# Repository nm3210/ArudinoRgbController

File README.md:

# Arudino Rgb(w) Project Collection
This repository contains a bunch of projects that I've created over the years for controlling various RGB (and sometimes RGBW) LED projects using arduinos uno's/teensy's. I have primarily been using the Eclipse-based [Sloeber](http://eclipse.baeyens.it/stable.php?OS=Windows) Arduino IDE which makes programming in C++ for the arduino platform much eaiser (especially if you're used to Eclipse).

## Main Projects:
* [ArudinoRgbController](ArudinoRgbController): This contains the original Atmega328 arduino (duo/uno) code that was used on a project to control some RGB LEDs (the simple four-lead ones) based on the time from a real-time clock (RTC) input. 

    The idea was to be a 'Visual Alarm', inasmuch that the LEDs would change color based on the time during the day. For this project, I also designed a circuit board with all the necessary RTC inputs and power for the LEDs which can be found on OSH Park [here](https://oshpark.com/shared_projects/ZrMcpgAp) (images of the circuit board below). 

* [RgbControllerWithIR](RgbControllerWithIR): This is an extension of the above ArudinoRgbController project that adds in the [IRremote library](https://github.com/z3t0/Arduino-IRremote) in order to control the colors a little easier.

    A *big* note: it was necessary to move the output pin for the blue RGB from pin 11 to pin 5 because of a conflict with the internal timer libraries and the IRremote ([see issue here](https://github.com/z3t0/Arduino-IRremote/issues/251)). This change required me to physically ripup the connection between pin 11 and the blue led transistor and then white wire a new connection to pin 5. Then the IR receiver was added to pin 2.

## Testing & Prototyping Projects:
### NeoPixel (WS2812B/SK6812, specifically RGBW strips)
* [NeoPixelTesting](NeoPixelTesting): This project plays around with the NeoPixel RGBW LED strips. I initially bought the [AdaFruit](https://www.adafruit.com/products/2868) stick of eight but eventually bought a roll of them off ebay (5m of 30LEDs/m).
* [MultiSegmentTesting](MultiSegmentTesting): This is an extension of the NeoPixelTesting project that adds in the ability to split up the strip into differnt arbitrary-length segments.

### RTC (DS1307)
* [RTC_SetTime](RTC_SetTime): Set/initialize the time of the DS1307 to the time at compile.
* [RTC_ReadTime](RTC_ReadTime): Read back the time on the DS1307 with the ability to add in extra seconds with a button press.
* [RTC_AlarmTesting](RTC_AlarmTesting): Test the [TimeAlarm](https://github.com/PaulStoffregen/TimeAlarms) library with the DS1307.

### Other/Misc
* [IrRemoteTesting](IrRemoteTesting): Test the incorporation of an IR receiver on an arduino.
* [ButtonTesting](ButtonTesting): Test the use of the AIN0 comparator on the atmega328 for use as a button.
* [HsiColor](HsiColor): Establishes the 'HSI' colorspace (from [here](http://blog.saikoled.com/post/43693602826/why-every-led-light-should-be-using-hsi)) instead of direct RGB, making it easier to do crossfading (used in the ArduinoRgbController project).

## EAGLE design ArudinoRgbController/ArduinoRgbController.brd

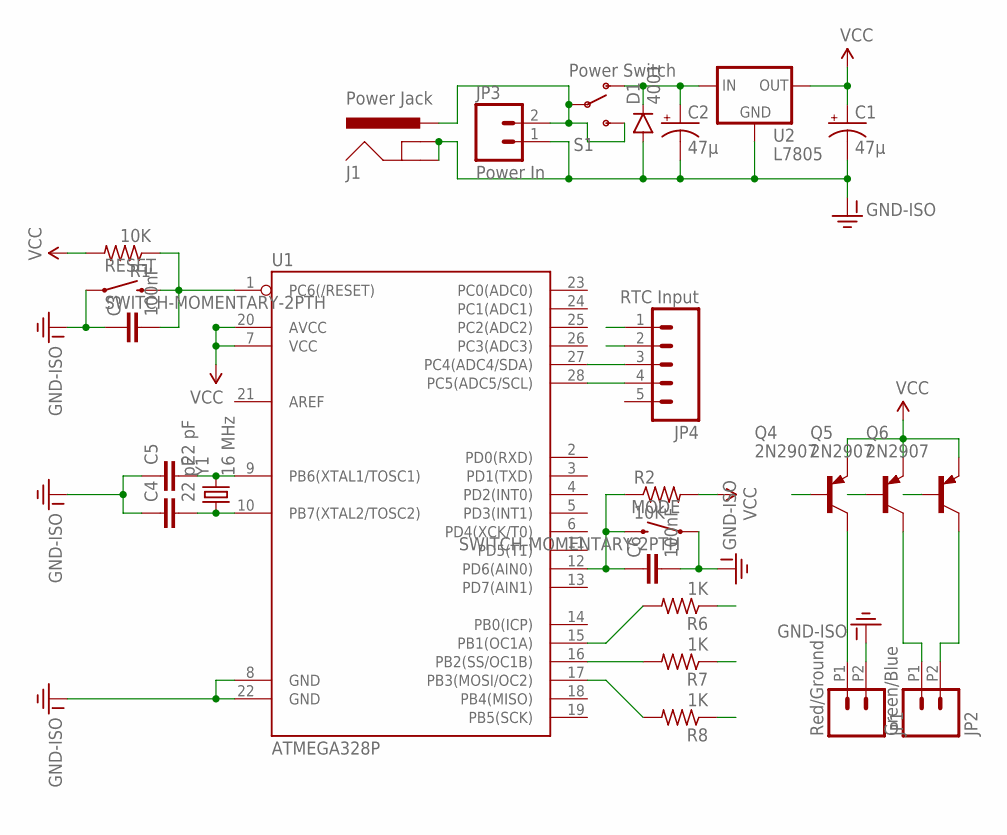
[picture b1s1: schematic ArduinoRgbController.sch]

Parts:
C1, C2: 47μ; ELECTROLYTIC_CAP
C3, C6: 100nF; CAP-PTH-SMALL
C4, C5: 22 pF; CAP-PTH-SMALL
D1: 4001; DIODE-1N4001
J1: Power Jack; POWER_JACK
JP1: Red/Ground; 1X02_2.54_SCREWTERM
JP2: Green/Blue; 1X02_2.54_SCREWTERM
JP3: Power In; SCREWTERMINAL-5MM-2
JP4: RTC Input; 1X05_LONGPADS
MODE: SWITCH-MOMENTARY-2PTH; TACTILE-PTH
Q4, Q5, Q6: 2N2907; TO92-EBC-OVAL
R1, R2: 10K; 0207/9
R6, R7, R8: 1K; 0207/9
RESET: SWITCH-MOMENTARY-2PTH; TACTILE-PTH
S1: Power Switch; SWITCH-SPDT
U1: ATMEGA328P; DIL28-3
U2: L7805; 78XXL
Y1: 16 MHz; HC49US

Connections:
BLUE: Q6.B, R8.1
BLUE_LINE: R8.2, U1.17 (PB3(MOSI/OC2))
BLUE_OUT: JP2.P2 (2), Q6.C
GND-ISO: C1.-, C2.-, C3.1, C4.1, C5.1, C6.2, D1.A, J1.GND, J1.GNDBREAK, JP1.P2 (2), JP3.1, JP4.1, MODE.1, RESET.1, U1.8 (GND), U1.22 (GND), U2.GND
GREEN: Q5.B, R7.1
GREEN_LINE: R7.2, U1.16 (PB2(SS/OC1B))
GREEN_OUT: JP2.P1 (1), Q5.C
unnamed: C5.2, U1.9 (PB6(XTAL1/TOSC1)), Y1.2
unnamed: C4.2, U1.10 (PB7(XTAL2/TOSC2)), Y1.1
PC4: JP4.3, U1.27 (PC4(ADC4/SDA))
PC5: JP4.4, U1.28 (PC5(ADC5/SCL))
RED: Q4.B, R6.1
RED_LINE: R6.2, U1.15 (PB1(OC1A))
RED_OUT: JP1.P1 (1), Q4.C
RESET_LINE: C3.2, R1.1, RESET.3 (2), U1.1 (PC6(/RESET))
SWITCH_LINE: C6.1, MODE.3 (2), R2.1, U1.12 (PD6(AIN0))
VCC: C1.+, JP4.2, Q4.E, Q5.E, Q6.E, R1.2, R2.2, U1.7 (VCC), U1.20 (AVCC), U2.OUT
VIN_POSTSWITCH: C2.+, D1.C, S1.1 (O), U2.IN
VIN_PRESWITCH: J1.PWR, JP3.2, S1.2, S1.3 (S)

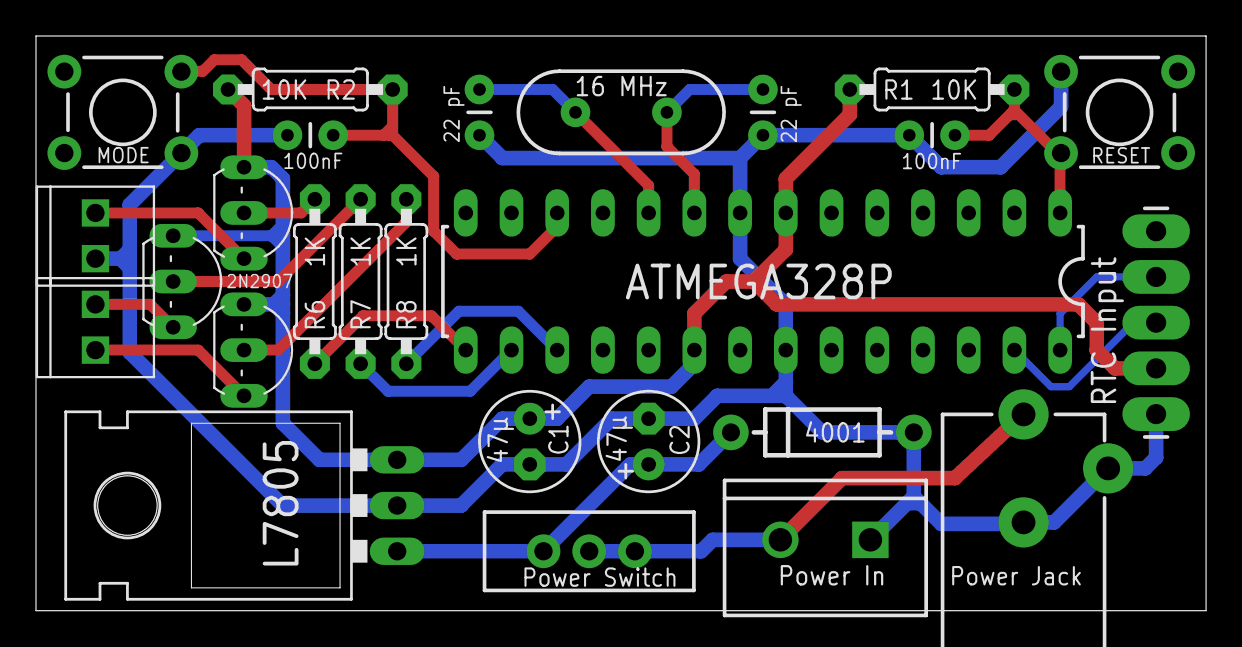
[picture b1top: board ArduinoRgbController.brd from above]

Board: 2 copper layers, 65.0 x 31.9 mm, 26 parts (0 on the bottom side), 19 nets.

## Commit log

2016-08-06 Initial (clean) project
    Base barebones arduino c++ project.
2016-08-06 Update to 'Revision1'
    This revision incorporates some simple RGB fading based on some code I
    found on stack echange.
2016-08-06 Adding RTC functions
    This commit adds the 'ReadTime' and 'SetTime' arguino sketches to
    control the time of the DS1307 RTC.
2016-08-07 Update to 'Revision 2' - HSI mode
    This update changed a LOT of the underlying color logic. Instead of
    trying to work things out in RGB space, it converts things to HSI which
    allows some really easy looping of colors. A left a lot of commented out
    code in this commit (for various trail/errors) that will get cleaned up
    later.
2016-08-07 Adding other testing sketches
    Adding the 'ButtonTesting' sketch which was an attempt at trying to
    figure out how to do a long-press; it seems to work fine on my proto
    board, but not at all on the final PCB/wired one. This also adds the
    'HsiColor' sketch which is where I ironed out all the bugs to HSI before
    adding it to the main ArduinoRgbController.
2016-08-12 Disable 'dynamic mode'
    The dynamic mode will be a bit trickier to figure out, this commit
    disables the alarms, switch statement, and related functions.
2016-08-12 Fix to alarms not working; added functions
    This commit adds the 'Alarm.delay(0)' which was needed to make all the
    alarms work. I also updated the alarm times to be more practical and
    added a couple 'adjustInt' and 'adjustSat' functions to make it easier
    to change the properties of a color.
2016-08-13 Adding 'AlarmTesting' sketch
    This sketch (not currently working) will check for alarm flags during
    the loop. The purpose will be to not rely on the Alarm.alarmRepeat(..)
    that isn't quite as flexible as I woud like. Hopefully this implemention
    will make the 'dynamic mode' work able.
2016-08-13 Update to get the alarm checking working
    This updates the 'AlarmTesting' sketch to actually work! It's just a
    simple check for time-of-day now.
2016-08-14 Change to the new alarm handler
    This commit uses the new alarm handler that was established within the
    'RTC_AlarmTesting' sketch. It also reintroduces the 'dynamic mode' (for
    testing). I also cleaned up a lot of the old function/variables.
2016-08-14 Minor color changes and code cleanup.
    This changes the 'orange' and 'violet'/'purple' colors to be a bit
    brighter. Also cleaned up some comments here and there.
2016-08-14 Fix for the count variable looping around
    This issue caused the colors to jump to green to red abruptly when
    things wrapped around. The fix keeps the count variable contained with a
    modulo.
2017-01-30 Moved all functions in the h file to the cpp file
    Not sure why I felt the need to put functions in the header file, but
    this commit moves them into the cpp file. This is the covention I plan
    on using in the future, where applicable.
2017-01-30 Adding new 'RgbControllerWithIR' project
    This new project adds an IR remote functionality to the RGB controller
    via the 'IRremote.h' library.
2017-02-21 Adding new NeoPixelTesting project
    This new project tests support of the Adafruit NeoPixel RGBW LED strip
    (using the WS2812 or SK6812 chip).
2017-02-21 Adding 'Color' struct
    Copying over the 'Color' struct from the ArduinoRgbController project.
2017-02-21 Updating 'Color' class to use RGBW
    Added support for RGBW Color. The NeoPixel I'm using has four built-in
    LEDs: RGBW, so this commit updates the necessary code to create hsi
    colors properly.
2017-02-21 Re-introduce crossfading into NeoPixel
    Port over the crossfading algorithm from ArduinoRgbController to this
    project (now a direct port now that we're in the HSI colorspace).
2017-02-21 Adding IrRemoteTesting project
    This project tests the IRremote library using a TSOP4838 IR receiver and
    various IR remotes.
2017-02-21 Try to use the atmega interrupts to trigger the IR
    This commit attempts to use the atmega interrupts in order to trigger
    the IR decoding process (in hindsight, I now understand that this
    already happens within the IRremote library).
2017-02-21 Using IRremote 'isIdle' call for reliability
    I found that using the 'isIdle' call while receiving a signal is
    essential in order to 'listen' to the entire length of the IR signal.
    This commit also makes a note that setting the 'TOLERANCE' variable
    within IRremoteInt.h (line 130 ish) to around 40 instead of 25 also
    helps with reliability -> changes to the library are not controlled
    here.
2017-02-21 Adding NeoPixel functionality to IrRemoteTesting
    Add the NeoPixel to this IrRemote project so we have something to
    control!
2017-02-21 Add more IR button lookups
    This adds a bunch more buttons from various remotes.
2017-02-21 Add new LightColor class and button actions
    The new LightColor class controls what mode the current LEDs are in
    (controlled via switch). The new button actions are defined under
    'checkModes..' and include things like on/off, brightness, etc.
2017-02-21 Added check for holding an IR button down (repeat)
    This checks whether the IR remote is sending an 0xFFFFFFFF which
    seemingly represents a 'resend' or 'repeat' concept. The logic in this
    commit checks for this value and then re-processes the last saved button
    press again. This allows the user to hold the (e.g.) brightness button
    down and have it repeatedly turn the brightness up/down.
2017-02-21 Add long-press detection for IR remote buttons
    This adds long-press detection to the IR remote buttons, allowing you to
    do more 'enhanced' features, if desired.
2017-02-22 Adding MultiSegmentTesting project
    This project takes the NeoPixel LED strip and separates it into
    different segments that can each have their own color/mode.
2017-02-22 Migration of IrRemote & Color structs into MultiSeg
    This commit pulls in a few of the other projects (IrRemoteTesting and
    NeoPixelTesting) for testing the multiple segments - helps to have
    someway to control things!
2017-02-22 Add long press and all-segment functions
    Add in the latest long-press commit from the IrRemoteTesting project.
    This commit also develops a way to control all the segments at once when
    desired, currently activated by a long-press, making it a lot easier to
    control the whole LED strip.
2017-02-22 Add blinking feature for currently selected segment
    This commit adds a 'blink' feature to the current segment to make it
    really easy to tell what segment is currently being modified.
2017-02-24 Adding Eagle Schematics
    Add the board/pcb schematics for the AndroidRgbController and
    RgbControllerWithIR projects.
2017-03-06 Putting schematics in a zip
    Git doesn't need to deal with all the xml lines in the board/schematic
    eagle files.
2017-03-08 Update for on/off controls
    This adds in the 'doAllSegments' concept for the normal on/off buttons,
    previously this functionality was just available when long-pressing the
    on/off button (now you can go into 'allSegment' mode and just click the
    button).
2017-03-08 New SegmentData structure
    Created a new SegmentData structure to contain all the relevant
    information about a single segment (modes, brightness, sat), making it a
    lot easier to deal with. And this'll make things easier for storing data
    on the EEPROM...
2017-03-08 Adding EepromTesting project
    This project uses the EEPROM on the arduino (using Teensy LC currently)
    and will be used to test the ability to save data when the board is
    offline/unpowered.
2017-03-08 Adding data structure 'putting' for EEPROM
    Test using the MultiSegment 'SegmentData' structure and writing/reading
    it off EEPROM.
2017-03-08 Testing putting multiple data structures
    This tests multiple data array structures and some test data.
2017-03-08 Adding EEPROM reading/writing to MultiSeg
    This incoporates the [very basic] EEPROM reading/writing into the
    multisegment project to allow the Teensy LC to remember the state of all
    the segments after it gets turned off.
2017-03-18 New EepromData class for loading/saving data
    This new class handles all the loading and saving of EEPROM data,
    featuring a saveChanges() function that only updates the fields that
    have been modified (thus saving EEPROM life/longevity).
2017-06-19 Added new 'rainbow' color mode for the LED strips.
    I have to work on the speed because it's really slow when doing ~150
    LEDs.
2017-06-24 Fixes for the new rainbow mode.
    Updated the rainbow mode to work better across segments (needed to use
    consistent divisors) and added a 'biasRed' method which helps pull out
    the red color more. This commit has been tested and seems to work well
    (minus EEPROM stuff that's still ongoing).
2017-06-24 Cleanup of comments
2019-01-20 Clean up some of the commented out code and comments
2019-01-20 Add better timezone and DST corrections
    This uses the Timezone library located at https://github.com/JChristensen/Timezone.
2019-01-20 Add calculation of sunrise and sunset times
    This is from the Dusk2Dawn library at https://github.com/dmkishi/Dusk2Dawn
2019-01-20 Add special alarms for sunrise/sunset events
2019-01-20 Incorporate sunAlarms into the alarm mode, turn orange at sunset
2019-01-20 Update alarm times and colors, now keep red light on all night
    This change is to better match the other visual alarm clocks on the market (ala amazon) that change to red round bedtime (and stay red all night) to indicate that red==sleep.
2019-01-20 Disable dynamic mode to stay under 32KB program memory
2019-01-20 Perform alarm action again after mode change
    This is helpful to keep the night color on if the modes are changed.
2019-01-20 Use a variable for the color being controlled with IR, move switch statement
    This makes the 'controlColor' something that can be referened and can now be changed within any mode. The purpose will be to modify the color of the overnight color (which is currently red).
2019-01-20 Use the controlColor for the nighttime/bedtime color (change w/ IR)
2019-01-20 Remove commented out code and update some comments
2019-01-20 Allow color and brightness changes (via IR) in any mode
2019-01-20 Allow adjustment of brightness (via IR) within color loops
2019-01-20 Hardcode (git submodule) library references for RgbControllerWithIR
    This adds in git submodules directly to the github repos for the libraries being used in the RgbControllerWithIR project. It should be noted that the Ethernet, SPI, SoftwareSerial, and Wire libraries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
2021-03-13 Remove ability to add time during for ReadTime sketch
2021-03-13 Move serial start to before serial prints
2021-03-13 Add UTC/timezone and compile time offsets when setting time
    The goal of this SetTime is to have the RTC (be it DS3231 or DS1307) be in UTC time and then other libraries can offset it from there.
2021-03-13 Update time alarms and remove RTC correction (hoping DS3231 will hold time)
2021-03-13 Remove unknown +3h sunrise/sunset offset (which maybe i need?)
2021-03-13 Remove unused IR control
    I realize this makes the name of this sketch (RgbControllerWithIR) totally pointless now and I should 'merge' it back in to the nominal 'ArduinoRgbController' sketch, but eh

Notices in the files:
parts and their libraries:
SparkFun-DigitalIC: Licensing: Creative Commons ShareAlike 4.0 International - https://creativecommons.org/licenses/by-sa/4.0
